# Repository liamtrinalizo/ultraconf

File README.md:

# idea
change before private

private

change after

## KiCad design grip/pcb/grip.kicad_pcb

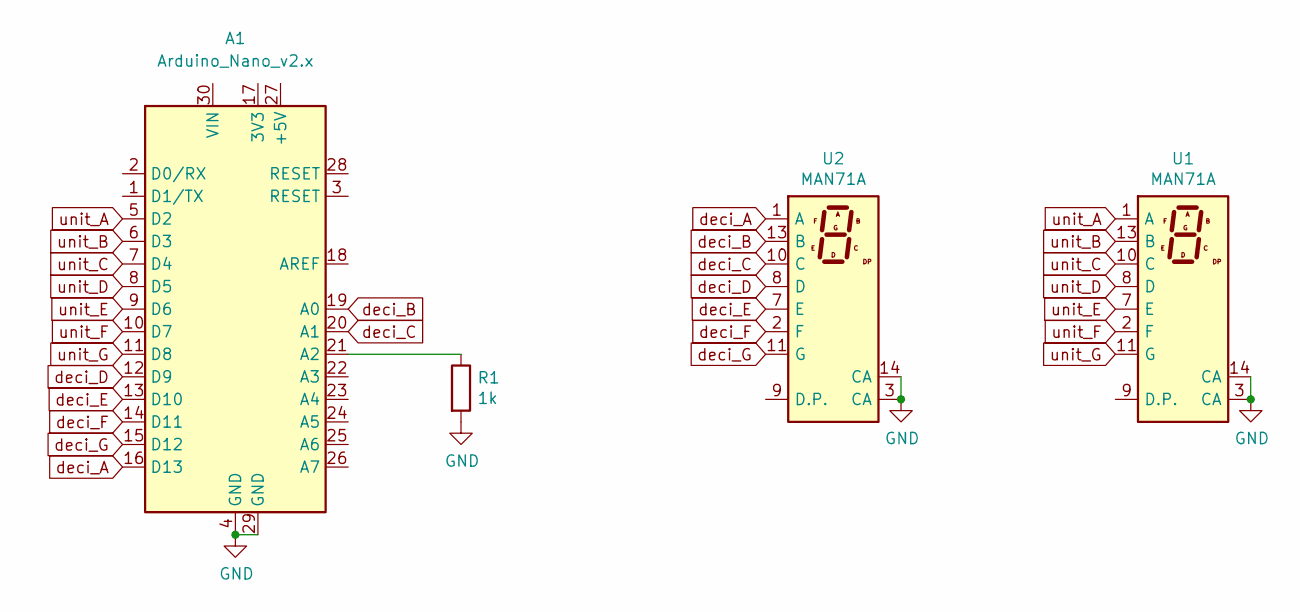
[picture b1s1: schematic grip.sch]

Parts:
A1: Arduino_Nano_v2.x; Arduino_Nano
R1: 1k; R_Axial_DIN0207_L6.3mm_D2.5mm_P10.16mm_Horizontal
U1, U2: MAN71A; CAI3191AH

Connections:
GND: A1.4 (GND), A1.29 (GND), R1.2, U1.3 (CA), U1.14 (CA), U2.3 (CA), U2.14 (CA)
unnamed: A1.21 (A2), R1.1
deci_A: A1.16 (D13), U2.1 (A)
deci_B: A1.19 (A0), U2.13 (B)
deci_C: A1.20 (A1), U2.10 (C)
deci_D: A1.12 (D9), U2.8 (D)
deci_E: A1.13 (D10), U2.7 (E)
deci_F: A1.14 (D11), U2.2 (F)
deci_G: A1.15 (D12), U2.11 (G)
unit_A: A1.5 (D2), U1.1 (A)
unit_B: A1.6 (D3), U1.13 (B)
unit_C: A1.7 (D4), U1.10 (C)
unit_D: A1.8 (D5), U1.8 (D)
unit_E: A1.9 (D6), U1.7 (E)
unit_F: A1.10 (D7), U1.2 (F)
unit_G: A1.11 (D8), U1.11 (G)

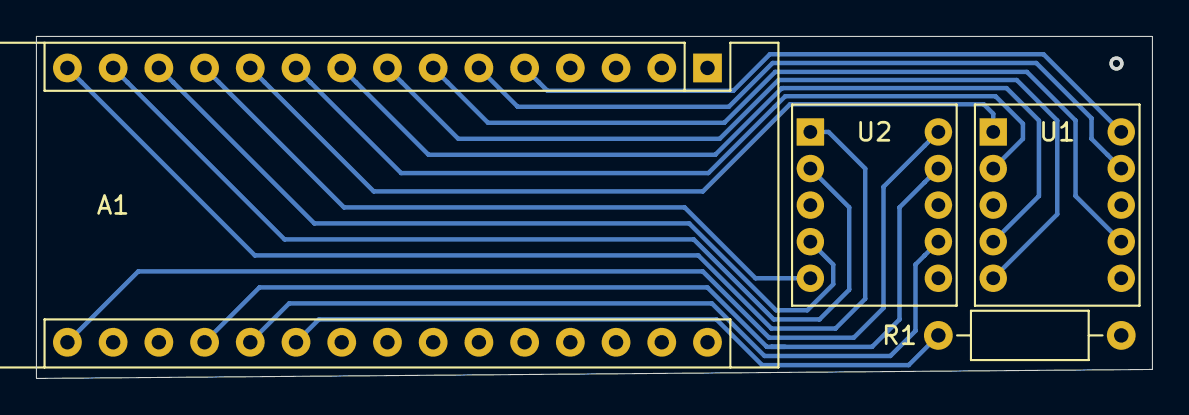
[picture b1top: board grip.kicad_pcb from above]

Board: 2 copper layers, 62.0 x 19.0 mm, 4 parts (0 on the bottom side), 16 nets.

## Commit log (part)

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2020-02-24 add portage make.conf
2020-02-24 git: disable prompt in mergetool
2020-02-24 scripts: add low battery env var warning
2020-02-24 vim: add diff custom color
2020-02-24 zsh: cargo vim: diffopt
2020-02-25 git: remove all flag in log aliases
2020-02-25 script: correct merge error
2020-02-25 zsh: add env var for pastel
2020-02-26 mutt: color management tags, emoji and diff
2020-03-01 tmux: add remind output to status,
    Add darkmode to imagemagick through X resources
2020-03-02 mutt: remove diff coloring
2020-03-02 zsh: add jira auto-completion
2020-03-04 xorg: unified all bg/fg to black/white
2020-03-07 zsh: move dotdir to .config/zsh
2020-03-16 Add script to delete useless histfiles cluttering homedir
2020-03-25 Remove old test files
2020-03-25 Add back xrb at startup
2020-03-26 Merge
2020-04-16 vim: add cscope and cleanup spelllang
2020-04-20 Profile: moved default dotfiles to .config
2020-04-20 mutt: add default appli for media attachments
2020-04-21 zsh: revert to bindkey -v and create nnn change dir function
2020-05-05 tmux: yank wwith y in copy mode
2020-05-13 Profile: reorder env var
2020-05-13 Scripts: add windows scripts
2020-05-13 Vim: remove duplicate, useless setting
2020-05-13 Scripts: add printer script
2020-05-13 vhdl: add missing config files
2020-05-25 Vim: diff color hl
2020-05-25 Mutt: rebind N and V for unread
2020-05-26 Zsh: correct ctrl+r search
2020-05-29 Grip: add pcb recue files
2020-05-30 Profile: Reorganize dotfiles in XDG dirs
2020-06-02 Git: set rebase false
2020-06-03 Script: correct elif screen.sh
2020-06-05 Mutt: Replace display by sxiv
2020-06-22 Git: Add autocorrect
2020-06-22 Mutt: Add mailcap entry and correct color
2020-06-23 Scripts: correct cleanup
2020-06-26 Vim: Add commit file jira task shortcut
2020-06-26 Mutt: add history save/search
2020-06-29 zsh: edit cmd line in vim
2020-06-30 Conf update
    zsh startx
    vim complete colorscheme
    profile xauthority
    mutt mailcap, binding
2020-07-01 Profile: remove superfluous GPG_TTY
2020-07-03 zsh: change for simple prompt with git branch display
2020-07-03 X11: add numlock and redshift to xinit
2020-07-06 Profile: correct Xressource location
2020-07-10 Jira: add config file to revision control
    Remove the leading "jira-" in filename to place in ~/.jira.d
2020-07-10 Zsh: move windows specific alias to new file
2020-07-13 Trans: add init config file to version ctrl
2020-07-14 Jira: add in-review command
2020-07-17 Jira: Correct line indentation
2020-07-23 Jira: Replace optional param with hugo template syntax
2020-07-23 Jira: add jira to remind script
2020-07-30 Vim: add persistent undo
2020-07-30 Zsh: remove nnn change dir
2020-08-04 zsh: add completion script for jira cmd
2020-08-04 Zsh: improved jira complete witout needing tmp file
2020-08-10 Jira: call jira list only if issue completion needed
2020-08-17 Zsh, Vim, Mutt, update
2020-08-18 Mutt: bold red index when important flag
2020-08-19 Mutt: add isync binding
2020-08-24 Vim: remove expandtab and duplicate
2020-08-25 jira: add issue id in cal display
2020-08-27 Tmux: update status bar with emoji
2020-09-03 Zsh: sorted aliases
2020-09-03 W3M: replace display by sxiv as default image viewer
2020-09-14 Script: replace fzf by fzy
2020-09-23 Jira: auto complete all project type
2020-09-23 Zsh: Add mutt alias
2020-09-25 Vim: Add .yml to files with spell auto enabled
2020-09-25 Zsh: autocomplete jira project in maj
    Some go-jira commands only accepts maj project names
2020-09-25 Mutt: Sync mailbox silently
2020-10-05 Vim: Add autowriteall and binding gz to wall
2020-10-05 Zsh: Reverse completion select with shift tab
2020-10-05 Git: Improved git l1 output
2020-10-05 Profile: pass default clipboard is primary
2020-10-09 Scripts: Script fixing duplicate definition with gentoo qt install
2020-10-13 Script: Improve workout script
2020-10-15 Ebuilds: create ebuild versioning folder add df ebuild
2020-10-16 Tmux: bind v to begin select in copy mode
2020-10-16 Ebuilds: df correct useflags of libsdl
2020-10-21 Jira: replacing args by options when possible
2020-10-22 Scripts: change title color for easier reading
2020-10-22 Mutt: move vim last in mailcal text
2020-11-03 bspwm: Add bspwmrc and sxhkdrc to revision ctrl
2020-11-03 vim: HeaderC command auto complete c source header
2020-11-03 Vim: add jira syntax
2020-11-03 zsh: python
2020-11-03 mailcal.sh: delete script
2020-11-12 Mutt: use 24 hour format
2020-11-12 Vim: add spelling language in default conf
2020-11-12 X11: correct xrdb loading in xinitrc
2020-11-12 workout.sh: replace type parameter by file
2020-11-12 update.sh: starting manual pkg auto update
2020-11-13 Vim: correct autocmd
2020-11-13 Jira: improve open/close worklog curstom cmd
    Update zsh completion script
2020-11-13 Mutt: correct mailcap
2020-11-13 gitNotif.sh: add script
2020-11-18 Heavy project structure modification
    Rename project to cooler name "ultraconf"
    Remove all not ultraconf project related files
    Add portage conf files
    Add the custom overlay ebuilds structure
    Add script to install normal user packages dotfiles
2020-11-19 forgot to remove grip folder
    correct dotfiles names
2020-11-21 zathura: add file
2020-11-21 zsh: Add cmd history nbr to zsh prompt
2020-11-21 zsh: correct prompt color
2020-11-22 magnet.sh: rename torrent after dl
2020-11-22 portage: update make.conf for distcc
2020-11-22 ultraconf.sh: add script parameters
2020-11-23 ultraconf.sh: add missing mkdir
2020-11-23 git: add d sub cmd when diff-so-fancy in not installed
2020-12-14 X11: remove unused xinit entries
2020-12-14 Correct ultraconf
2020-12-20 vim: fix special highlight color
2021-01-05 zsh: add gnuplot and ffmpeg aliases
2021-01-05 replace tabs by spaces
2021-01-07 zsh: add freerdp alias
2021-01-07 zsh: add ip alias
2021-01-08 jira: add worklog open/edit/close sub cmd
2021-01-08 zsh: append .config/zsh/completion for completion script path
2021-01-08 ultraconf.sh: install and source .zprofile
2021-01-08 add readme
2021-01-12 jiraWorklogs.sh: remove escape chars suppression
2021-01-12 X11: correct multi monitor and wm hotkeys
2021-01-14 vim: remove netrw tree style because of bug with symlink
2021-01-14 mutt: correct vcal mailcap
    disable prompt when saving mail another folder
2021-01-24 X11 correct one screen setup
2021-02-01 status.sh: display num of new messages
2021-02-01 follow window when swaping
2021-02-01 add pathConv script
2021-02-01 ultraconf.sh: correct zprofile install
2021-02-01 add lighter background for quartus
2021-02-01 mutt: sync mailbox when reading mail
2021-02-04 update.sh: Correct brave install when beta release
2021-02-08 vim: correct viminfofile setting
2021-03-17 add default color val to gnuplot
2021-03-17 correct abook,vim macros in mutt
2021-03-17 add char to digraph list
2021-04-13 add abook file
2021-04-19 aliases for zsh and sub cmd for jira
2021-04-20 Add binding to sxhkd update screen script
2021-04-20 Mailcap and abook update for mutt
2021-04-20 add elinks dotfile location in zprofile
2021-04-20 add french C to digraph list
2021-04-20 Quote jira worklogs before piping to remind
2021-04-20 focus only window on super (shift) c in bspwm
2021-04-22 remove fzy from jira worklog subcmd to use zsh completion instead
2021-04-29 default mail in raw text
2021-04-29 correct jira zsh completion script
2021-04-29 add openscad dotfile to revision ctrl
2021-04-29 add X11 conf remaping caps to compose
2021-05-05 add grap ebuild
    rename overlay directory to ebuilds
2021-05-05 change vim tab and trail characters for easier readability
2021-05-05 sxhkd replace shift+hjkl binding to move floating windows
2021-05-05 tmux selected window is bold green in status
2021-05-06 rename man to manuals
2021-05-19 add printf manual
2021-05-19 zsh correct jira worklog completion
2021-05-19 emoji.sh put selected in clipboard
2021-05-19 add jira_syntax manual
2021-05-20 vim set previous mappings for normal mode only
2021-06-09 add german manual
2021-06-09 jira fix worklog add cmd
2021-06-18 grep exclude binar in vim and zsh
2021-06-18 translate engine is google
2021-06-23 zsh disable broken svn completion
2021-07-01 remove numbering in zsh grep alias
2021-07-01 adding vim mapping for simpler escape
2021-07-13 vim add default setting for 10 lines bottom padding in search
2021-07-14 add script for mailing embeded images
2021-07-15 bspwm add shortcut to flip parent node of focussed win
2021-07-15 git blame cmd split info from code in vim
2021-08-06 sxhkd only on binding to flip windows
2021-08-06 digraph add circonflex
2021-08-06 jiraWorklogs reorganize remind formating
2021-08-06 jira change worklog time param syntax
2021-08-06 add license
2021-08-17 xinit add check if programs are available
2021-08-17 update.sh add check to halt system after update
2021-08-31 update ebuilds
2021-08-31 rename dotfiles to match XDG_CONFIG structure
2021-08-31 portage default jobs to 5
2021-08-31 update.sh remove old brave ebuilds after copy
2021-08-31 add TODO
2021-09-30 zsh disable sort on jira completion
2021-09-30 zsh add function to hide latex aux and log files
2021-09-30 update.sh do not remove previous brave ebuild
2021-10-15 vim add .tex file for spell activation
2021-10-15 zsh add function to get dictionary info on word
2021-10-15 add portage patches in installation makefile
2021-11-05 clean up elinks conf file
2021-11-05 sxhkd add binding to translated screen selection
2021-11-05 man jira correct advanced table
2021-11-08 add alias to access Imagemagick online cli doc
2021-11-17 add jira templates to git
2021-11-18 update jira template
2021-11-20 zsh add pretty file rename function
2021-11-30 manuals german add adj according
2021-12-12 vim add python make programme autocmd
2022-01-13 vim support fenced code block in jira syntax
2022-01-13 zsh add dark mode sxiv "dxiv" function
2022-01-13 mutt add mailcap for xls document
2022-01-13 add visual studio project makefile
2022-02-16 ebuild update pmbootstrap ebuild
2022-02-17 mutt add binding to display calendar and normal attachments
2022-02-20 update german manual
2022-02-20 zsh add hiit and timer function
2022-02-20 screen.sh autodetect screen name
2022-02-21 vim update with windows special conf
2022-02-21 add cygwin path conversion
2022-02-21 add windows zsh aliases to git
2022-02-21 add script to compile nmake project from cygwin
2022-02-21 symlink zshenv to zlogin to access alias from login shell
2022-02-23 change elink binding j/k to scroll up/down
2022-03-02 add youtube zsh function
2022-03-02 unmask unstable packages in portage
2022-03-04 Add CLIBROWSER var to handle command line browser settings
2022-03-16 vim change spelling error to white foreground
2022-03-18 add eselect fontconfig info
2022-03-18 remove underline in zsh syntax
2022-04-19 vim remove manual auto folding
2022-04-20 vim set cscope config only when cscope.out exist
    Cscope config collide with ctags automatic jump to selection
    If CTRL-] ask prompt for selection, comment cscope config
2022-04-22 fix makefile for scripts installation
2022-04-22 sync mail with offlineimap when isync is not installed
2022-05-09 vim default view is tree style in netrw
2022-05-09 zsh add sqlformat and music alias
2022-05-11 add FUZZYFIND env var to contain fuzzy finder command
2022-05-11 fix mailsync error redirection
2022-09-23 add windows aliases
2022-09-23 vim add markdown makeprg and syntax file
    status line now shows the highlight group under cursor
2022-09-23 zsh invert upper lower in sqlformat alias
2022-09-23 zsh cleaning up old aliases
2022-10-24 fix nocompatible setttings
    nocompatible was resetting some config and thus needs to be set first
    to avoid override
2022-10-24 zsh add alias for easy elinks dump
2022-11-10 zsh: enable comments in interactive shell
2022-11-14 zsh correct keep push/push aliases
2022-12-03 zsh update aliases
2023-01-27 git commit hook only check for added TODO changes
2023-01-27 fix pythonpath variable
2023-01-27 mutt disable sidebar by default
2023-08-17 add st config file
2023-08-17 fix dbxcli keep alias for windows
2023-08-17 fix indentation matching in vim markdown syntax
2023-08-17 add vim syntax for ledger
2025-03-17 clean settings in vimrc
    add markdown chapter status line
    disable Q mapping
